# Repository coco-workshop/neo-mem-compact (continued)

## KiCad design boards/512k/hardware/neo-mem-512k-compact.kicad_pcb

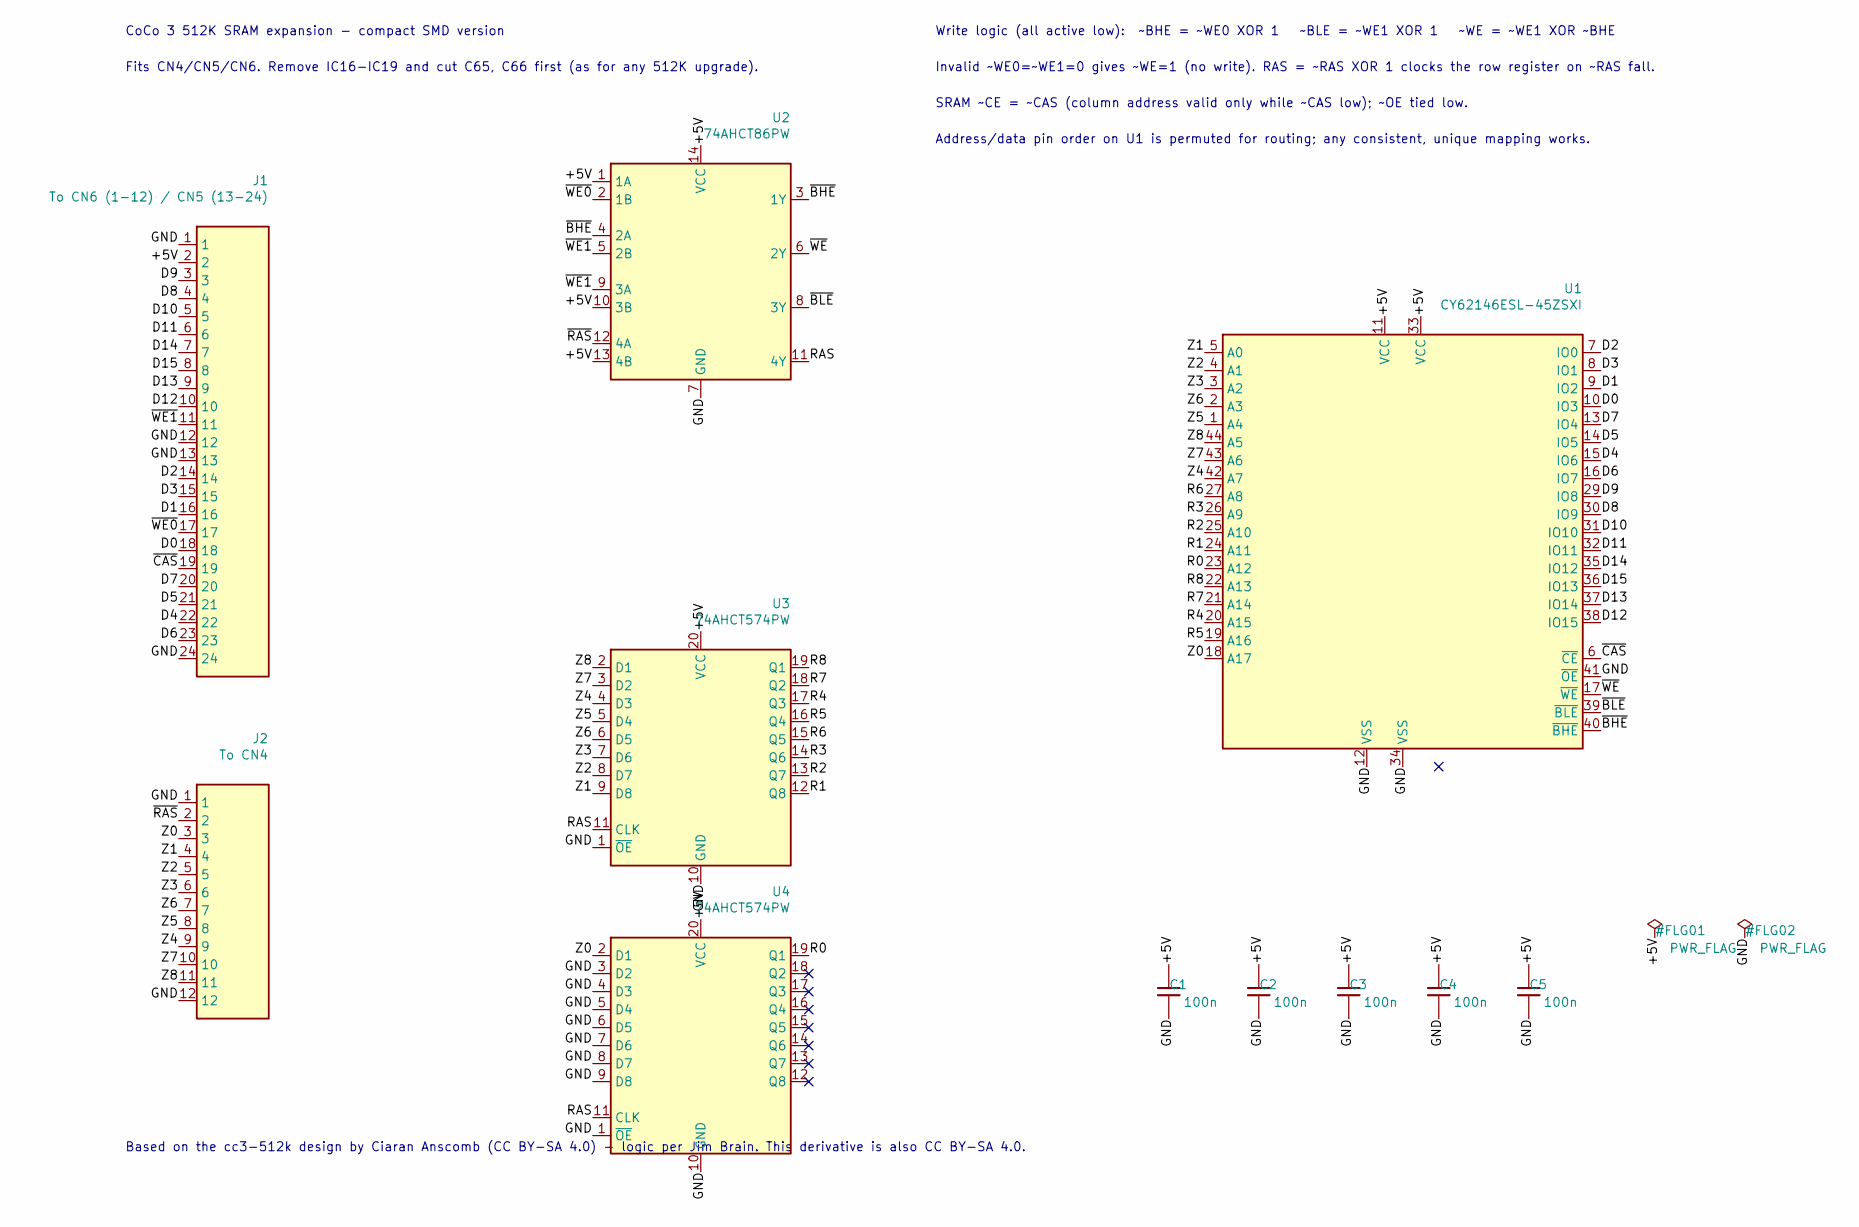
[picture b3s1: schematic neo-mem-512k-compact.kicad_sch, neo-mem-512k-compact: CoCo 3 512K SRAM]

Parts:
C1, C2, C3, C4, C5: 100n; C_0402_1005Metric
J1: To CN6 (1-12) / CN5 (13-24); PinHeader_1x24_P2.54mm_Vertical
J2: To CN4; PinHeader_1x12_P2.54mm_Vertical
U1: CY62146ESL-45ZSXI; TSOP-II-44_10.16x18.41mm_P0.8mm
U2: 74AHCT86PW; TSSOP-14_4.4x5mm_P0.65mm
U3, U4: 74AHCT574PW; TSSOP-20_4.4x6.5mm_P0.65mm

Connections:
/+5V: C1.1, C2.1, C3.1, C4.1, C5.1, J1.2, U1.11 (VCC), U1.33 (VCC), U2.1 (1A), U2.10 (3B), U2.13 (4B), U2.14 (VCC), U3.20 (VCC), U4.20 (VCC)
/D0: J1.18, U1.10 (IO3)
/D1: J1.16, U1.9 (IO2)
/D2: J1.14, U1.7 (IO0)
/D3: J1.15, U1.8 (IO1)
/D4: J1.22, U1.15 (IO6)
/D5: J1.21, U1.14 (IO5)
/D6: J1.23, U1.16 (IO7)
/D7: J1.20, U1.13 (IO4)
/D8: J1.4, U1.30 (IO9)
/D9: J1.3, U1.29 (IO8)
/D10: J1.5, U1.31 (IO10)
/D11: J1.6, U1.32 (IO11)
/D12: J1.10, U1.38 (IO15)
/D13: J1.9, U1.37 (IO14)
/D14: J1.7, U1.35 (IO12)
/D15: J1.8, U1.36 (IO13)
/GND: C1.2, C2.2, C3.2, C4.2, C5.2, J1.1, J1.12, J1.13, J1.24, J2.1, J2.12, U1.12 (VSS), U1.34 (VSS), U1.41 (~OE), U2.7 (GND), U3.1 (~OE), U3.10 (GND), U4.1 (~OE), U4.3 (D2), U4.4 (D3), U4.5 (D4), U4.6 (D5), U4.7 (D6), U4.8 (D7), U4.9 (D8), U4.10 (GND)
/R0: U1.23 (A12), U4.19 (Q1)
/R1: U1.24 (A11), U3.12 (Q8)
/R2: U1.25 (A10), U3.13 (Q7)
/R3: U1.26 (A9), U3.14 (Q6)
/R4: U1.20 (A15), U3.17 (Q3)
/R5: U1.19 (A16), U3.16 (Q4)
/R6: U1.27 (A8), U3.15 (Q5)
/R7: U1.21 (A14), U3.18 (Q2)
/R8: U1.22 (A13), U3.19 (Q1)
/RAS: U2.11 (4Y), U3.11 (CLK), U4.11 (CLK)
/Z0: J2.3, U1.18 (A17), U4.2 (D1)
/Z1: J2.4, U1.5 (A0), U3.9 (D8)
/Z2: J2.5, U1.4 (A1), U3.8 (D7)
/Z3: J2.6, U1.3 (A2), U3.7 (D6)
/Z4: J2.9, U1.42 (A7), U3.4 (D3)
/Z5: J2.8, U1.1 (A4), U3.5 (D4)
/Z6: J2.7, U1.2 (A3), U3.6 (D5)
/Z7: J2.10, U1.43 (A6), U3.3 (D2)
/Z8: J2.11, U1.44 (A5), U3.2 (D1)
/~BHE: U1.40 (~BHE), U2.3 (1Y), U2.4 (2A)
/~BLE: U1.39 (~BLE), U2.8 (3Y)
/~CAS: J1.19, U1.6 (~CE)
/~RAS: J2.2, U2.12 (4A)
/~WE0: J1.17, U2.2 (1B)
/~WE1: J1.11, U2.5 (2B), U2.9 (3A)
/~WE: U1.17 (~WE), U2.6 (2Y)

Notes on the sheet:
CoCo 3 512K SRAM expansion - compact SMD version
Fits CN4/CN5/CN6. Remove IC16-IC19 and cut C65, C66 first (as for any 512K upgrade).
Write logic (all active low): ~BHE = ~WE0 XOR 1 ~BLE = ~WE1 XOR 1 ~WE = ~WE1 XOR ~BHE
Invalid ~WE0=~WE1=0 gives ~WE=1 (no write). RAS = ~RAS XOR 1 clocks the row register on ~RAS fall.
SRAM ~CE = ~CAS (column address valid only while ~CAS low); ~OE tied low.
Address/data pin order on U1 is permuted for routing; any consistent, unique mapping works.
Based on the cc3-512k design by Ciaran Anscomb (CC BY-SA 4.0) - logic per Jim Brain. This derivative is also CC BY-SA 4.0.

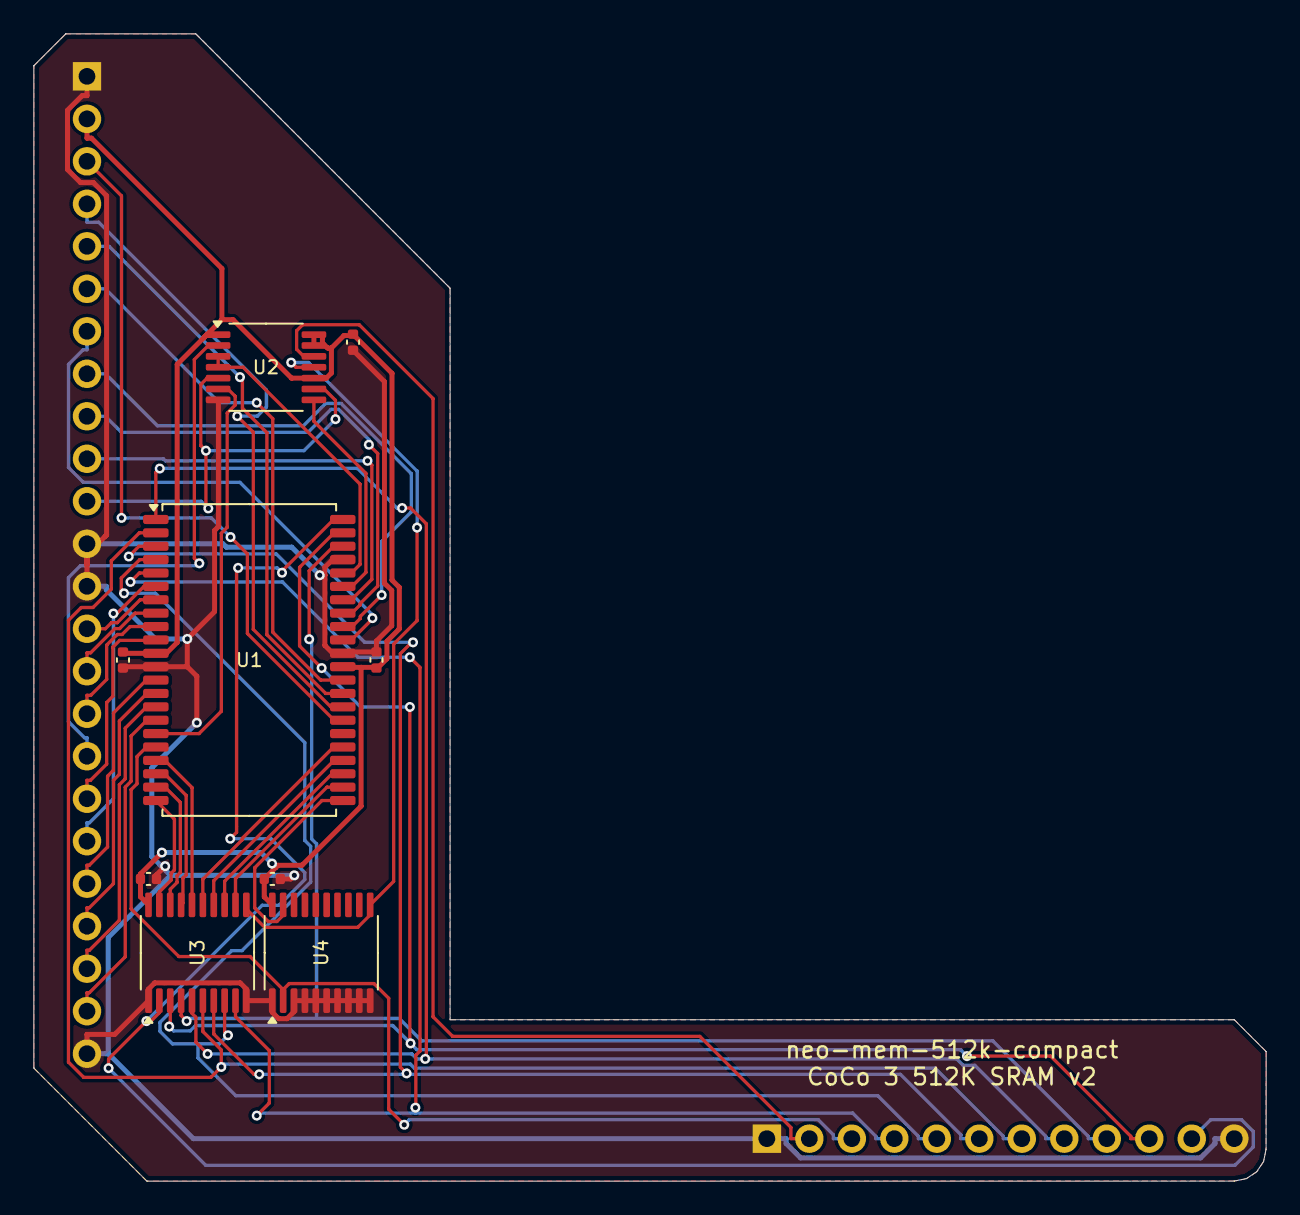
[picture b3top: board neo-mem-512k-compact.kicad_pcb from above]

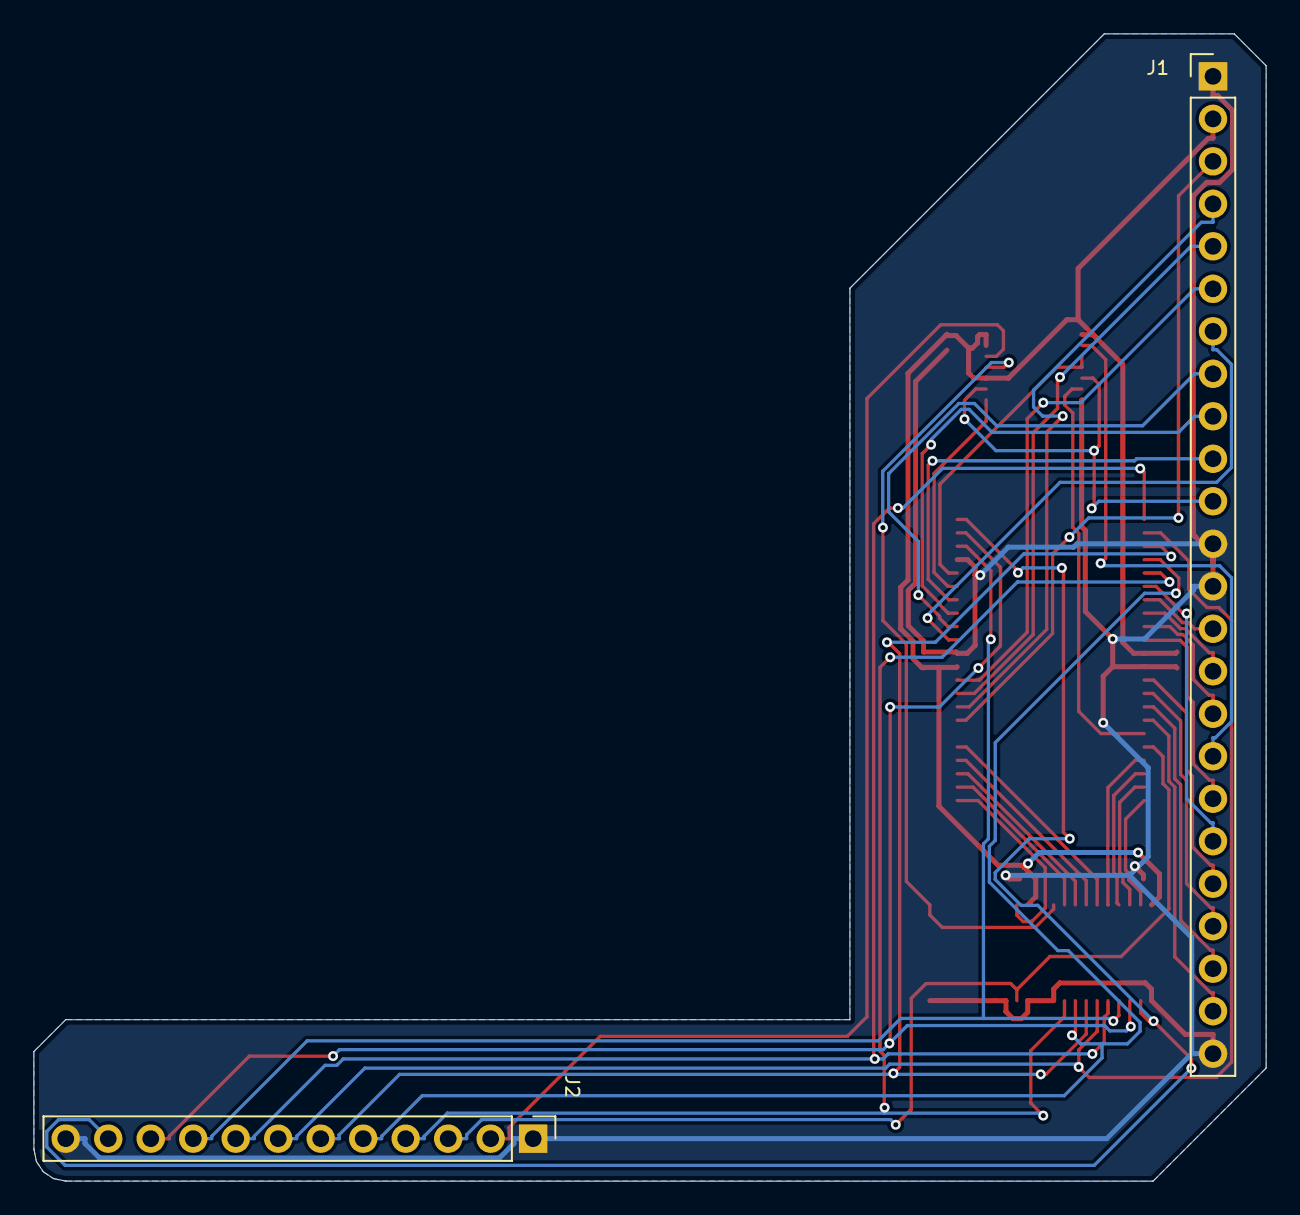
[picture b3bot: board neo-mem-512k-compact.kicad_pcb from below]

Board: 2 copper layers, 73.7 x 68.6 mm, 11 parts (2 on the bottom side), 44 nets.

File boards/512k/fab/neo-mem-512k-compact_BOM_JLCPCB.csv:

Comment,Designator,Footprint,LCSC Part #
CY62146ESL-45ZSXI 256Kx16 SRAM (5V),U1,TSOP-II-44_10.16x18.41mm_P0.8mm,C2953196
SN74AHCT86PWR quad XOR (alt: 74AHCT86PW C554719),U2,TSSOP-14_4.4x5mm_P0.65mm,C471866
74VHCT574AFT(BE) octal D flip-flop (alt: 74AHCT574PW C282328),"U3,U4",TSSOP-20_4.4x6.5mm_P0.65mm,C7421311
100nF 16V X7R 0402,"C1,C2,C3,C4,C5",C_0402_1005Metric,C1525

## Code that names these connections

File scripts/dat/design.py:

"""DAT board netlist: CPU-socket interposer carrying an ATF1504AS (logic in cpld/dat2m.v).

J1 is a 40-pin interposer: a wire-wrap (long-tail) DIP-40 socket whose tails pass through
the board into the CoCo 3's CPU socket; the 6809/6309 plugs into its top. Every CPU pin
passes straight through - the CPLD only listens (all CPLD CPU-side pins are inputs).
"""
import json, os

# 6809E / 6309E pinout (only the pins we tap or power from)
CPU = {1: 'GND', 7: '+5V',
       **{8 + i: 'A%d' % i for i in range(16)},          # pins 8-23: A0-A15
       24: 'D7', 25: 'D6', 28: 'D3', 30: 'D1', 31: 'D0',
       32: 'RW', 34: 'E', 35: 'Q', 37: '~RESET'}

# ATF1504AS-10AU44 (TQFP-44) - same pinout as EPM7064 TQFP-44
CPLD_VCC = [9, 17, 29, 41]
CPLD_GND = [4, 16, 24, 36]
CPLD_JTAG = {1: 'TDI', 7: 'TMS', 26: 'TCK', 32: 'TDO'}
CPLD_DEDICATED = {37: 'E', 38: 'Q', 39: '~RESET', 40: 'RW'}   # GCLK1, OE1, GCLR, OE2/GCLK2
CPLD_IO = [2, 3, 5, 6, 8, 10, 11, 12, 13, 14, 15, 18, 19, 20, 21, 22, 23, 25, 27, 28,
           30, 31, 33, 34, 35, 42, 43, 44]
IO_SIGNALS = ['A%d' % i for i in range(16)] + ['D0', 'D1', 'D3', 'D6', 'D7', 'EN2M', 'BANK0', 'BANK1', 'LED_FASTn']

U1 = {p: '+5V' for p in CPLD_VCC}
U1.update({p: 'GND' for p in CPLD_GND})
U1.update(CPLD_JTAG)
U1.update(CPLD_DEDICATED)
_assign = os.path.join(os.path.dirname(__file__), 'assign.json')
if os.path.exists(_assign):
    U1.update({int(k): v for k, v in json.load(open(_assign)).items()})

# 10-pin JTAG, Atmel ATDH1150USB / Altera USB-Blaster layout
JTAG = {1: 'TCK', 2: 'GND', 3: 'TDO', 4: '+5V', 5: 'TMS', 9: 'TDI', 10: 'GND'}   # 6,7,8 NC
# Bank output to the memory board: a 2x2 header laid out like the GIME-Z's bank header.
# Pins 1/3 (outer column, toward the tab edge) carry B0/B1; pins 2/4 (inner column) are
# ground. The bank lines pass through 100R series resistors so a cable plugged in the wrong
# way can't short a CPLD output.
J2 = {1: 'B0', 2: 'GND', 3: 'B1', 4: 'GND'}
# Turbo LED header: case LED anode to pin 1 (+5V), cathode to pin 2; R3 limits the current.
J4 = {1: '+5V', 2: 'LED_K'}

PARTS = {
    'J1': dict(value='CPU interposer (40-pin wire-wrap socket)', fp='Package_DIP:DIP-40_W15.24mm', pins=CPU),
    'U1': dict(value='ATF1504AS-10AU44', fp='Package_QFP:TQFP-44_10x10mm_P0.8mm', pins=U1),
    'J2': dict(value='BANK out 2x2 (B col / G col)', fp='Connector_PinHeader_2.54mm:PinHeader_2x02_P2.54mm_Vertical', pins=J2),
    'J4': dict(value='Turbo LED', fp='Connector_PinHeader_2.54mm:PinHeader_1x02_P2.54mm_Vertical', pins=J4),
    'R1': dict(value='100', fp='Resistor_SMD:R_0402_1005Metric', pins={1: 'BANK0', 2: 'B0'}),
    'R2': dict(value='100', fp='Resistor_SMD:R_0402_1005Metric', pins={1: 'BANK1', 2: 'B1'}),
    'R3': dict(value='470', fp='Resistor_SMD:R_0402_1005Metric', pins={1: 'LED_K', 2: 'LED_FASTn'}),
    'J3': dict(value='JTAG', fp='Connector_PinHeader_2.54mm:PinHeader_2x05_P2.54mm_Vertical', pins=JTAG),
    # 3-pad solder jumper on the back, bridged 1-2 at the factory (EN2M = 1, 2 MB mode).
    # 512K mode: cut the 1-2 bridge and bridge 2-3 (EN2M = 0).
    'JP1': dict(value='2MB/512K', fp='Jumper:SolderJumper-3_P1.3mm_Bridged12_RoundedPad1.0x1.5mm', pins={1: '+5V', 2: 'EN2M', 3: 'GND'}),
}
CAPS = ['C1', 'C2', 'C3', 'C4']
for c in CAPS:
    PARTS[c] = dict(value='100n', fp='Capacitor_SMD:C_0402_1005Metric', pins={1: '+5V', 2: 'GND'})
